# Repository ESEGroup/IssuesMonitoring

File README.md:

# IssuesMonitoring
COS603/2017 Development Project

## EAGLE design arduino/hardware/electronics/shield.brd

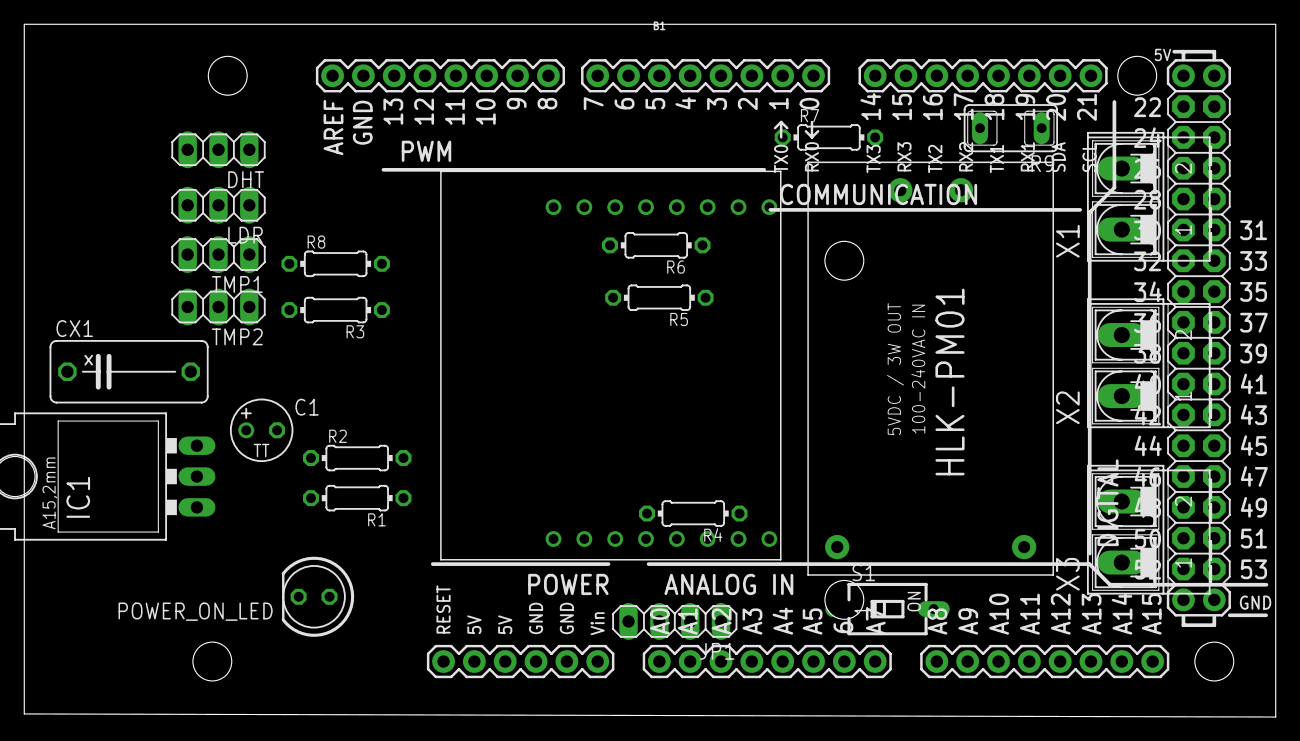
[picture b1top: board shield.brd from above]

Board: 2 copper layers, 103.1 x 57.1 mm, 25 parts (0 on the bottom side), 21 nets, no tracks yet.

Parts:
B1: ARDUINO_MEGA_R3FULL; ARDUINO_MEGA
C1: 1uf; TT2D5
CX1: 0.1uF; XC10B5
DHT: 1X03
IC1: 3.3V; 317TL
JP1: 1X04
LDR: 1X03
POWER_ON_LED: LED5MM
R1, R3, R5, R6, R7: 330; 0204/7
R2: 541; 0204/7
R4: 110; 0204/7
R8: 4.7k; 0204/7
R9: S2220
S1: SD4-01
TMP1, TMP2: 1X03
U$1: HLK-PM01
U$4: ESP8266_SHIELD
X1, X2, X3: AK500/2-H

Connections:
5V: B1.5V@0, DHT.3, LDR.3, R3.1, R8.2, TMP1.3, TMP2.3
DC+: S1.2, U$1.DC+
DHT: B1.5, DHT.1
ESP8266_RX: B1.14, R7.2
ESP8266_TX: B1.15, U$4.TXD
GND0: B1.GND@0, POWER_ON_LED.K
GND1: B1.GND@1, C1.-, CX1.2, JP1.4, R2.2, R5.1, U$1.DC-, U$4.GND
GND4: B1.GND@4, DHT.2, LDR.2, TMP1.2, TMP2.2
LDR: B1.4, LDR.1
unnamed: R9.1, U$1.AC2, X1.2, X2.2, X3.2
unnamed: POWER_ON_LED.A, R3.2
unnamed: IC1.1, R1.2, R2.1
unnamed: R5.2, R6.1
unnamed: R6.2, R7.1, U$4.RXD
unnamed: R9.2, U$1.AC1, X1.1, X2.1, X3.1
unnamed: R4.2, U$4.CH_PD
POWER_SUPPLY_3.3V: C1.+, IC1.2, R1.1, R4.1, U$4.VCC
POWER_SUPPLY_5V: B1.VIN, CX1.1, IC1.3, JP1.1, S1.1
RELAY_1: B1.A1, JP1.2
RELAY_2: B1.A0, JP1.3
TMP: B1.3, R8.1, TMP1.1, TMP2.1

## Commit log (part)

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2017-05-01 Add existing lab user to lab from a 'manage' page
2017-05-01 Update config instructions
2017-05-02 Add confirmation message for sign up
2017-05-02 Fix db, minor code fixes
2017-05-02 Notificar Responsavel sobre cadastro de usuario
2017-05-02 Add confirmation messages
2017-05-02 Add more confirmation messages
2017-05-02 Retry on all DB errors
2017-05-02 Implement mail sender after system user signup in the server
2017-05-02 Fix typo
2017-05-02 fix mail sender
2017-05-02 Add config.py.example again
2017-05-03 Fix system user/admin instantiation
2017-05-03 Update class diagram
2017-05-03 Fix admin typo and add new route
2017-05-03 Fix send email about new user
2017-05-03 Add Selenium Test suites for TestPlans 1 and 2
2017-05-10 Implement a production ready wsgi server, minor fixes, force SECRET_KEY setup
2017-05-10 Fix execution instructions
2017-05-17 [arduino] adding libs for the temperature sensor
2017-05-17 [arduino] adding list of tutorials
2017-05-17 List users currently in the lab
2017-05-17 List/Edit/Remove lab users
2017-05-17 Edit/Remove system users
2017-05-17 MyDenox daily lab members logs
2017-05-18 notify users and admin if environment conditions are outside the comfort zone
2017-05-18 Add arduino model and controller
2017-05-18 Modify Zona_Conforto Table, create Arduino Table and fix zona_conforto methods
2017-05-19 Parse lab_id from messages and fix logs display
2017-05-20 check conditions for different labs
2017-05-20 Remove lumin config from web
2017-05-20 Fix web routes
2017-05-20 Fixed errors. Formatted IssuesMonitoring.ino
2017-05-20 Finish record arduino measurements
2017-05-21 Fix check-lights
2017-05-21 Add equipment temperature verification
2017-05-21 Adding modification to lights verification
2017-05-21 Optimize queries in conditions checks
2017-05-22 Update Class and ER diagrams
2017-05-26 Start redesign of site
2017-05-26 Fix a typo in labs.html
2017-05-26 Add image to choose labs button
2017-05-28 Add sliders to register lab form
2017-05-28 Add range sliders for choosing temperature bounds
2017-05-28 Add slider for humidity
2017-05-28 Improve project folder organization
2017-05-28 Create page for lab-user registration
2017-05-28 Create page for system-user registrarion
2017-05-28 Add temporary links to other pages in navbar
2017-05-29 Fix submit button label for user-lab registration page
2017-05-29 Fix parser imap error and send_email typo
2017-05-29 requirements doc updated
2017-05-29 [arduino] updating scenarios
2017-05-30 Create Casos de Testes
2017-05-31 Create page for attendance log
2017-05-31 Change page title CSS
2017-05-31 Create page for altering comfort zone of lab
2017-05-31 Add all option icons for lab management
2017-06-01 Make static templates dynamic
2017-06-02 Fix password field layout for neat-form
2017-06-02 Implement error message in login screen
2017-06-02 Fix error/success messages, make login work
2017-06-02 Make error message positioning work
2017-06-02 Make templates dynamic, fix views and backend to fit new design, minor fixes
2017-06-03 Update log_presenca to show lab users currently present in lab
2017-06-03 Create page for displaying lab-users associated to lab
2017-06-03 Make templates dynamic, fix server requests
2017-06-03 Minor fixes
2017-06-04 Add page for approving system user
2017-06-04 Create backend, minor fixes and improvements
2017-06-04 Fix alterar_dados_cadastrais.html
2017-06-04 Fix register lab submit
2017-06-04 Fix check_environment method name
2017-06-04 Fix user_id not showing in lista_mebros
2017-06-05 Adding test for environment conditions
2017-06-05 Add Casos de Teste
2017-06-05 Add Planejamento de Testes
2017-06-05 Hotifx: change words Parser and Arduino in forms for others which are more likely to be understood by an average user
2017-06-05 Upload finished user manual for Release 2
2017-06-06 Add Casos de Testes
2017-06-06 Add Testes Selenium
2017-06-07 Create Planejamento
2017-06-07 Planejamento Release 3
2017-06-14 Hotfix: fix presence log timestamp
2017-06-17 Checking environment conditions in an interval
2017-06-17 Mostrar ID em usuarios presentes e Mover Log de Presenca para abaixo da tabela
2017-06-17 Alterar Dados Cadastrais vira Alterar Configuracoes do Laboratorio
2017-06-17 Padronizar maiusculas e minusculas
2017-06-18 Fix timestamp
2017-06-18 Add syste-status page
2017-06-18 Adding line chart option for environment conditions
2017-06-18 Hotfix: fix reset_presenca timestamp
2017-06-18 Hide logout button if user is not authenticated
2017-06-19 Hotfix: fix parser timestamp
2017-06-19 Finished system-status
2017-06-19 Adding presence log table and environment conditions table to report
2017-06-19 Fix Log_Parser on create_db.py
2017-06-19 Hotfix: Fix system-status
2017-06-19 Clean codebase
2017-06-19 Hotfix: fix timestamp
2017-06-20 Update content before displaying the second page
2017-06-21 Add some sanity checks to graphs page
2017-06-21 [Arduino] server test with http
2017-06-22 PlanodeTeste
2017-06-23 Roll back on modifications
2017-06-24 Fix UI
2017-06-24 Implement Lab deletion
2017-06-24 Fix labels
2017-06-25 Adding calendar to choose date and time
2017-06-25 Changing checkbox to radio
2017-06-25 Adding temperature chart for equipments
2017-06-25 Create frontend for deleting a system user
2017-06-25 Fixing equipments list
2017-06-25 Add anomalias.html and change report icon
2017-06-25 Add enviar_email_acao_realizada
2017-06-25 Create and backend
2017-06-25 Add anomalia.png and fix FK lab_id in Log_Anomalias table
2017-06-25 Create default data in DB
2017-06-25 Make parser part of the server
2017-06-25 Show tables for report
2017-06-25 Change resolution of images
2017-06-25 Improve pages for Errors 404 and 500
2017-06-25 Change menu option text to display different outputs if logged out
2017-06-25 Create pdf report
2017-06-25 Fix imports
2017-06-25 Fix requirements
2017-06-25 Create back button on error pages
2017-06-25 Allow deleting users.
2017-06-25 Start work on the equipment manager
2017-06-26 Make registering an equipment almost work and add confirmation icon
2017-06-26 Minor bug fixes
2017-06-26 Fix cadastrar_equipamento
2017-06-26 Casos de Teste-Testlink
2017-06-26 Manter dos dados de Laboratório
2017-06-26 [Arduino] Sending full JSON package. TODO: fix sent data
2017-06-26 Fix gerenciar_equipamentos
2017-06-26 Implement lab-user removal
2017-06-26 Add files via upload
    Update Class and ER Diagrams
2017-06-26 Implement anomaly registration model
2017-06-26 Fix config file
2017-06-26 Remove debug prints
2017-06-26 [WIP]
2017-06-26 Fix delete button size
2017-06-26 Implement lab's hardware deletion
2017-06-26 Add registrar_anomalia to check methods
2017-06-26 Fix mail sender when anomaly is solved
2017-06-26 Allow to solve anomaly
2017-06-26 Fix registrar_acao
2017-06-26 Commit HTML
2017-06-26 Hotfix: labels
2017-06-27 Add name and description to Hardware
2017-06-27 Specify anomaly, between more than max or less than min, minor fixes
2017-06-27 Add sanity checks to mostra-grafico
2017-06-27 Add Equip data to anomaly
2017-06-28 Fix lab icon size inconsistencies in gerenciar.html as well.
2017-06-28 Added schematic (incomplete)
2017-06-28 [Arduino emulador] Added! Can improve by adding random variable for light
2017-06-28 Display -Not Available- message in manage user menu if trying to edit own user
2017-06-28 [Arduino] json sent via HTTP
2017-06-28 [Arduino] json configured to send data to server
2017-06-28 Fix emulador_arduino
2017-06-28 Add files to deploy app on heroku
2017-06-28 Fix anomaly detection
2017-06-28 Remove dead code, minor fixes
2017-06-29 Remove the files for heroku
2017-06-29 Create MyDenox log and display its status
2017-06-29 Fix admin_autenticado value in some views
2017-06-29 Properly detect MyDenox status
2017-06-29 Add sanity check to grafico.html
2017-06-29 Display temperature/humidity as int
2017-06-29 Import new date picker
2017-06-29 Improve -Display Graphs- webpage design adding a radio input
2017-06-29 Show that parser is offline if fail to connect with IMAP server
2017-06-29 Display lab id
2017-06-29 Update anomaly value when ignoring it to avoid flooding the mail box
2017-06-29 Minor fix
2017-06-29 Fix anomaly update
2017-06-29 Only save action when save button is clicked instead of instantly
2017-06-29 Display submenu when page from submenu is open
2017-06-29 Make datepicker work
2017-06-29 Add arduino supprot to cadastrar-equipamento
2017-06-29 Display parent Arduino's name, minor fix
2017-06-29 Implement time picker using WickedPicker
2017-06-30 Make date and time pickers work
2017-06-30 Fix messages and wrong login error
2017-06-30 Add exception message to mail error
2017-07-01 Add user manuel in doc (Word) format
2017-07-01 Localized datepicker to PT-BR and improve overall stability
2017-07-01 second commit
2017-07-01 Alert inconsistencies in accounts (MyDenox and Server)
2017-07-01 Make dropdown radio dynamic
2017-07-01 alter user
2017-07-01 Redo relatorio.html to fit new datepicker and interface
2017-07-01 Format radio inputs in lista_equipamentos.html
2017-07-01 finish alter user
2017-07-01 Fix parser update time
2017-07-01 Create user sys alter
2017-07-01 Fix cadastro-equipamento
2017-07-01 Fix input radios when registering equipment
2017-07-01 Clean lista_equipamentos.js of the loop checkage
2017-07-01 Remove zona-conforto for arduinos
2017-07-01 Create User_Sys editing
2017-07-01 Fix equip's names radio-button in mostrar-grafico
2017-07-01 Create Edit Equip Method
2017-07-02 Add alterar_senha method
2017-07-02 Add alterar_senha.html
2017-07-02 Fix all edit pages
2017-07-02 Finish alterar_senha
2017-07-02 Fix emulador-arduino
2017-07-02 Fix git markup in anomalia.html
2017-07-02 Fix charts for lab temperature
2017-07-02 Fix all charts
2017-07-02 Re-raise erros in debug to make debugging easier
2017-07-02 Update 'Manual do Usuário'
2017-07-02 Switch from radio input to select input in lista_equipamentos.html and alterar_equipament.html
2017-07-02 Switch from radio input to select input in grafico.html
2017-07-02 Change machine/arduino abstraction, fix report
2017-07-02 Include missing files
2017-07-02 Hide error messages before requesting report
2017-07-02 Properly display dates and unity of values
2017-07-02 Make calendars start in todays date and end in tomorrows date
2017-07-02 Update ER diagram and class diagram
2017-07-03 Fix chart backend
2017-07-03 Update equip temp-data with emulator
2017-07-03 Add chart_title
2017-07-03 Run wkhtmltopdf in GNU/Linux headless
2017-07-03 Hotfix
2017-07-03 Re-add removed functions (apparently it's not dead code oops)
2017-07-03 Hotfixes
2017-07-03 Remove log file from git
2017-07-03 Stream generated PDF, make workers asynchronous
2017-07-03 Debug log_presença
2017-07-03 Fix log_presença
2017-07-03 Add success message to aprovar.js
2017-07-03 Display MyDenox error when viewing present users
2017-07-03 Register anomaly when parser fails to connect to IMAP server
2017-07-03 Fix presence log, waiting for datepicker frontend fix
2017-07-03 Fix datepickers initial value to today and tomorrow
2017-07-03 Make lab ID appear in a more elegant manner
2017-07-03 Fix create_db.py syntax error
2017-07-03 Start to fix out of place buttons
2017-07-03 Finish fixing buttons positioning in all pages
2017-07-03 Make all return buttons in forms to be displayed below forms instead of inside them
2017-07-03 Make success/error messages disappear when going to a different menu
2017-07-03 Make 404 error image 10% bigger
2017-07-04 Update diagrams
2017-07-04 Fix redirect
2017-07-04 Make changes to remove all messages when switching views
2017-07-04 Removed Laboratorio from login side-bar
2017-07-04 Fix nav-bar label
2017-07-04 Add modal to show charts
2017-07-04 Add export date range to chart title
2017-07-04 Fix arduino route
2017-07-04 Make datepicker sliders appear behind modal window
2017-07-05 Convert temp/humidity to int
2017-07-05 Fix anomalies to solve filter
2017-07-05 Fix create_db.py, now working correctly
2017-07-05 Display error/success messages when appropriate, minor fix
2017-07-05 Caso de Teste- TestLink

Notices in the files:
parts and their libraries:
SparkFun-Boards: Licensing: Creative Commons ShareAlike 4.0 International - https://creativecommons.org/licenses/by-sa/4.0
